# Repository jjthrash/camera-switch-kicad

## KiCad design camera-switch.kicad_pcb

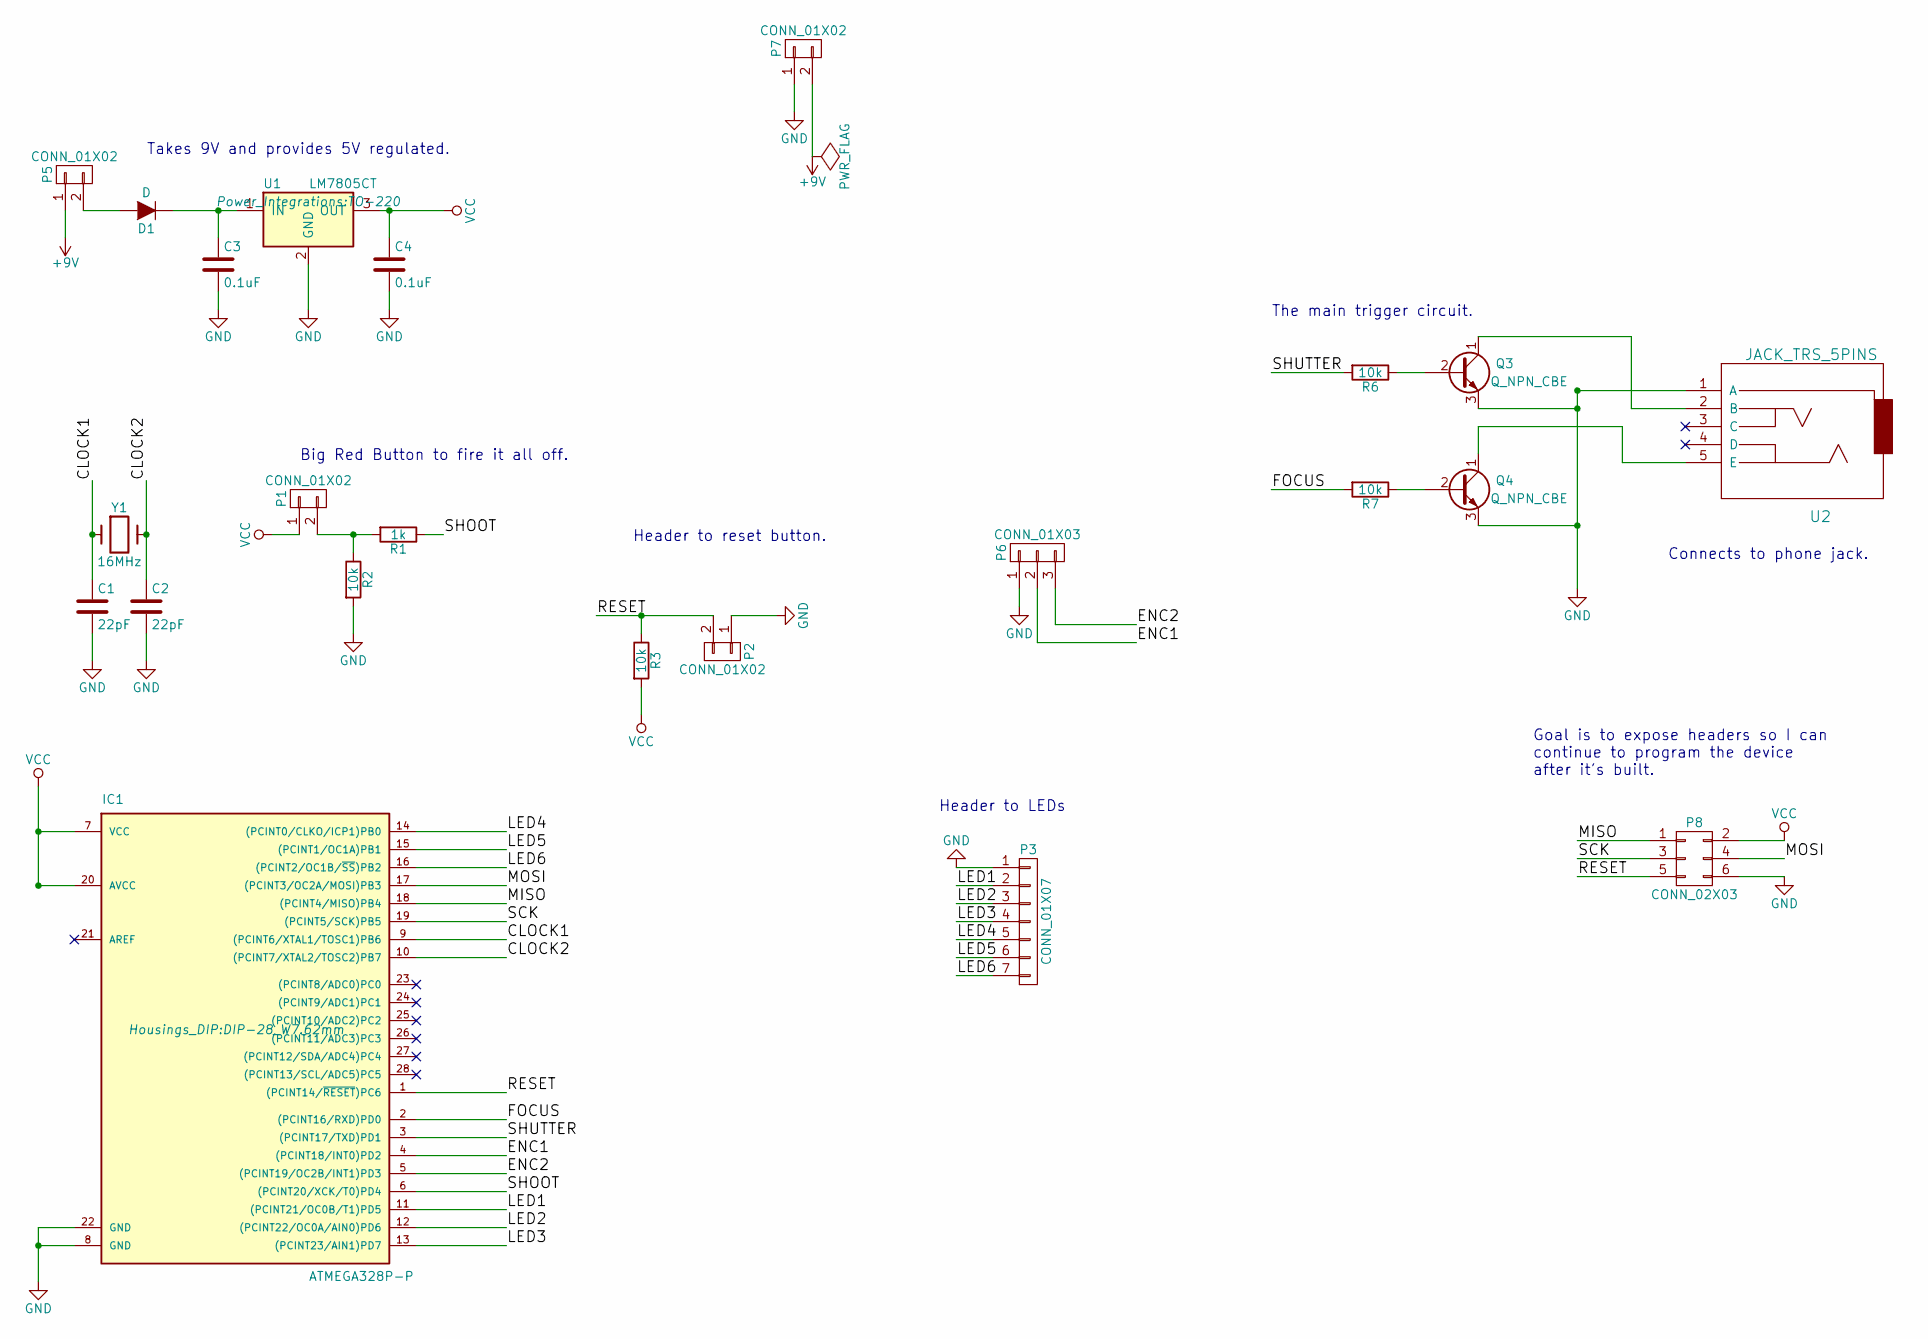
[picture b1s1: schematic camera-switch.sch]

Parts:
C1, C2: 22pF; C_Disc_D3_P2.5
C3, C4: 0.1uF; C_Disc_D6_P5
D1: D; Diode_DO-41_SOD81_Horizontal_RM10
IC1: ATMEGA328P-P; DIP-28_W7.62mm
P1, P2, P5, P7: CONN_01X02; Pin_Header_Straight_1x02
P3: CONN_01X07; Pin_Header_Straight_1x07
P6: CONN_01X03; Pin_Header_Straight_1x03
P8: CONN_02X03; Pin_Header_Straight_2x03
Q3, Q4: Q_NPN_CBE; TO-92_Inline_Narrow_Oval
R1: 1k; Resistor_Horizontal_RM10mm
R2, R3, R6, R7: 10k; Resistor_Horizontal_RM10mm
U1: LM7805CT; TO-220
U2: JACK_TRS_5PINS; audio_jack
Y1: 16MHz; Crystal_HC49-U_Vertical

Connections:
+9V: P5.1, P7.2
/CLOCK1: C1.1, IC1.9 ((PCINT6/XTAL1/TOSC1)PB6), Y1.1
/CLOCK2: C2.1, IC1.10 ((PCINT7/XTAL2/TOSC2)PB7), Y1.2
/ENC1: IC1.4 ((PCINT18/INT0)PD2), P6.2
/ENC2: IC1.5 ((PCINT19/OC2B/INT1)PD3), P6.3
/FOCUS: IC1.2 ((PCINT16/RXD)PD0), R7.2
/LED1: IC1.11 ((PCINT21/OC0B/T1)PD5), P3.2
/LED2: IC1.12 ((PCINT22/OC0A/AIN0)PD6), P3.3
/LED3: IC1.13 ((PCINT23/AIN1)PD7), P3.4
/LED4: IC1.14 ((PCINT0/CLKO/ICP1)PB0), P3.5
/LED5: IC1.15 ((PCINT1/OC1A)PB1), P3.6
/LED6: IC1.16 ((PCINT2/OC1B/~SS~)PB2), P3.7
/MISO: IC1.18 ((PCINT4/MISO)PB4), P8.1
/MOSI: IC1.17 ((PCINT3/OC2A/MOSI)PB3), P8.4
/RESET: IC1.1 ((PCINT14/~RESET~)PC6), P2.2, P8.5, R3.1
/SCK: IC1.19 ((PCINT5/SCK)PB5), P8.3
/SHOOT: IC1.6 ((PCINT20/XCK/T0)PD4), R1.1
/SHUTTER: IC1.3 ((PCINT17/TXD)PD1), R6.2
GND: C1.2, C2.2, C3.2, C4.2, IC1.8 (GND), IC1.22 (GND), P2.1, P3.1, P6.1, P7.1, P8.6, Q3.3 (E), Q4.3 (E), R2.2, U1.2 (GND), U2.1 (A)
unnamed: C3.1, D1.1 (K), U1.1 (IN)
unnamed: D1.2 (A), P5.2
unnamed: P1.2, R1.2, R2.1
unnamed: Q3.1 (C), U2.2 (B)
unnamed: Q3.2 (B), R6.1
unnamed: Q4.1 (C), U2.5 (E)
unnamed: Q4.2 (B), R7.1
VCC: C4.1, IC1.7 (VCC), IC1.20 (AVCC), P1.1, P8.2, R3.2, U1.3 (OUT)

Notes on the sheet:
Takes 9V and provides 5V regulated.
Connects to phone jack.
The main trigger circuit.
Goal is to expose headers so I can continue to program the device after it's built.
Header to reset button.
Big Red Button to fire it all off.
Header to LEDs

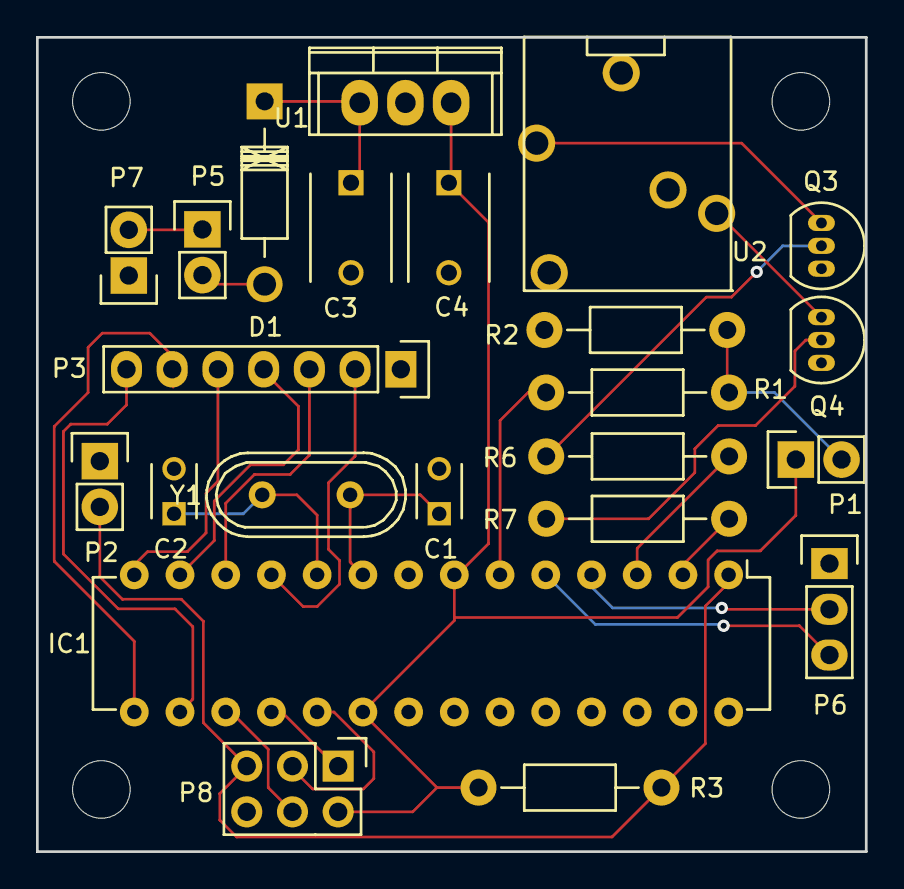
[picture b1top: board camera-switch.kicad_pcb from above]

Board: 2 copper layers, 46.1 x 45.2 mm, 23 parts (0 on the bottom side), 27 nets.

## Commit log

2016-08-30 Initial commit
    PCB is laid out, schematic is tested on breadboard.
